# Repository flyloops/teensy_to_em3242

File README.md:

# teensy_to_em3242 
Shield for Teensy3.2 with headers for Connecting to the EM3242 angle sensor IC via the 
angle_sensor_em3242 breakout board. 

* [Schematic (PDF)](teensy_to_em3242.pdf)
* [Bill-of-materials](BOM.txt)

# Top View: 

# Bottom View:

# License: 
Creative Commons Attribution 4.0 International CC BY 4.0

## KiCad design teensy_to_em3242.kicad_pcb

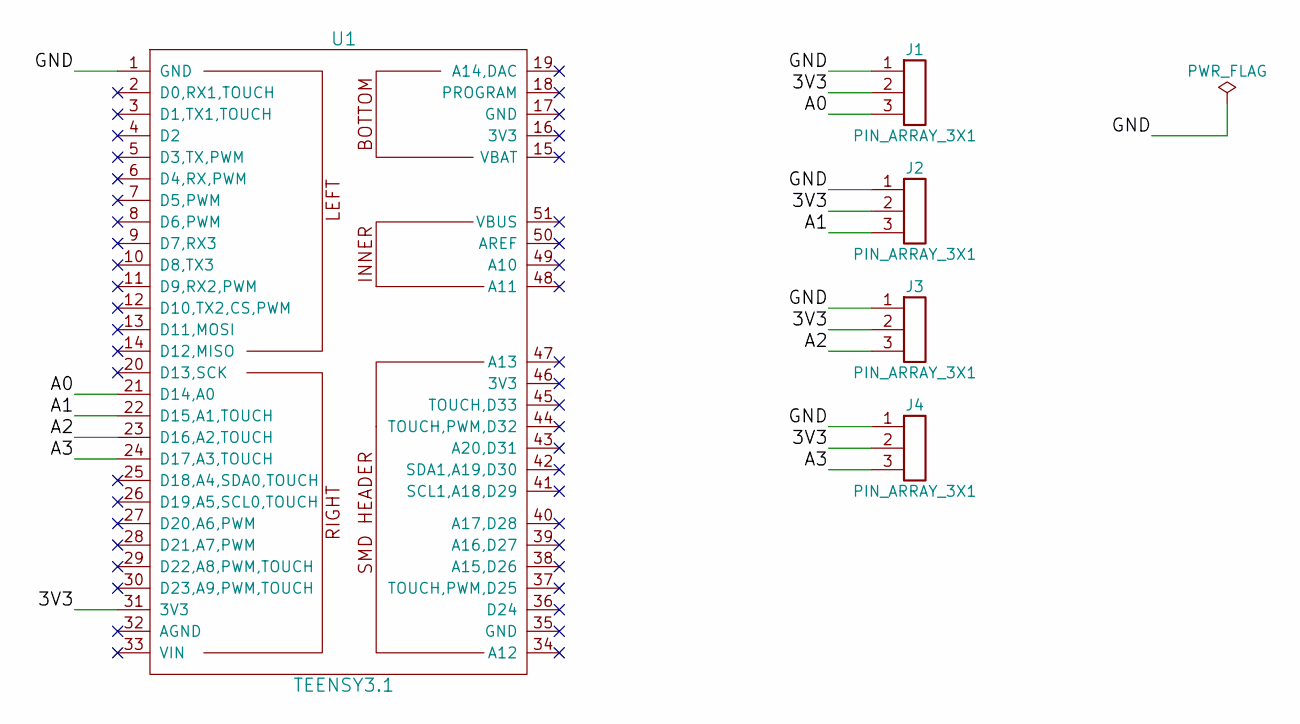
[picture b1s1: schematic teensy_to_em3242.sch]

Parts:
J1, J2, J3, J4: PIN_ARRAY_3X1; HEADER_3X1
U1: TEENSY3.1; TEENSY3X

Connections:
/3V3: J1.2, J2.2, J3.2, J4.2, U1.31 (3V3)
/A0: J1.3, U1.21 (D14,A0)
/A1: J2.3, U1.22 (D15,A1,TOUCH)
/A2: J3.3, U1.23 (D16,A2,TOUCH)
/A3: J4.3, U1.24 (D17,A3,TOUCH)
/GND: J1.1, J2.1, J3.1, J4.1, U1.1 (GND)

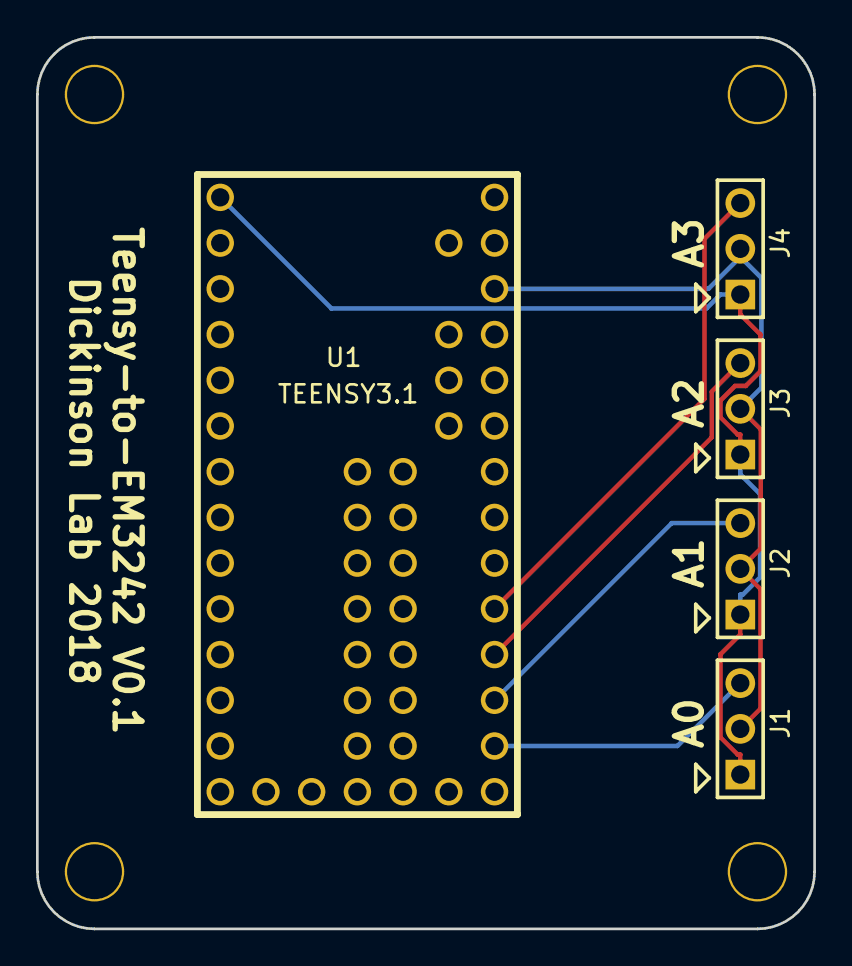
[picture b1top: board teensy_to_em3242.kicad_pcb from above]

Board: 2 copper layers, 43.2 x 49.5 mm, 9 parts (0 on the bottom side), 6 nets.

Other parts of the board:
M1, M2, M3, M4: VAL**; MOUNT_HOLE_4_40

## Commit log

2018-01-13 Project creation.
2018-01-17 Shortened board so that it is less the 50mm x 50mm. Added markings for pin #1 on sensor headers.
2018-01-17 Added PDF of schematic and link to it in README.
2018-01-17 Added bill-of-materials and link to it README.
